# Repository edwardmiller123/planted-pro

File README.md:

# planted-pro
This is the planted-pro plant monitor. It is my first electronics project and the goal was to create a full product end to end (mostly) from scratch. The repo aims to provide all the resources needed to build your very own if you so wished.

There is also the [planted-pro companion app](https://github.com/edwardmiller123/planted-pro-app)! Special thanks to [my wife](https://github.com/LucyRMCodes) for helping with this.

## Firmware
### Requirements
- [ARM GNU Toolchain](https://developer.arm.com/downloads/-/gnu-rm) - download the correct one for your system
- make
	- If on windows you can use a windows version like [Gnuwin32](https://gnuwin32.sourceforge.net/packages/make.htm)

- A device with the STLINK firmware. (For flashing main board) This could be an [official STlink debugger](https://uk.rs-online.com/web/p/debuggers-in-circuit-emulators/1827791) or a [nucleo board](https://www.st.com/en/evaluation-tools/nucleo-f446re.html)
- [OpenOCD](https://openocd.org/pages/getting-openocd.html) (For flashing main board)
	- [STLINK Tools](https://github.com/stlink-org/stlink) - Optional alternative
- gdb-multiarch (for flashing and debugging)

### Building
Compile the firmware with,
```
make fw
```

By default the fw is compiled without any log lines and with the debug LED on the main board disabled. To enable these simply run,
```
make fw LOGLEVEL={log level} (-B)
```
where {log level} ranges from 0 to 4 with 0 being FATAL and 4 being DEBUG. You may need to force a full rebuild with `-B` for make to pick up the symbol changes.

### Flashing The Board

## Main board
### Requirements
- [Kicad](https://www.kicad.org/)
- make
	- If on windows you can use a windows version like [Gnuwin32](https://gnuwin32.sourceforge.net/packages/make.htm)

### Exporting Fabrication Files
The gerber and drill files for the main board can be exported from kicad by running,
```
make pcb
```
This will create a `zip` of all the nessecary files ready to be sent to your favourite PCB manufacturer.

### Schematic
You can export a `pdf` of the schematic with,
```
make schematic
```

## Case
The case was designed in Tinkercad. STL files can be found in the `case` directory but you can also play with the original project online [here](https://www.tinkercad.com/things/aGYA4L6WpCP-planted-pro-v3).
Included in the `case` directory is a project file for [Bambu Studio](https://bambulab.com/en/download/studio) as I was printing on a [Bambu X1 Carbon](https://uk.store.bambulab.com/collections/x1-series) at [work](https://www.codethink.co.uk/). If using a different printer youll need to do the slicing yourself or you can send the `stl` files off to your favourite printing house.

## Constructing

### Requirements
- See previous sections for software requirements

You can generate all the nessecary files for contruction all at once by running,
```
make all
```

A full parts list can be found [here](docs/parts_list.md) in the docs folder along with data sheets for the MCU/ICs on the board and any external modules. 

# TODO
- Decrease the resistor values on the battery charge monitor to reduce noise

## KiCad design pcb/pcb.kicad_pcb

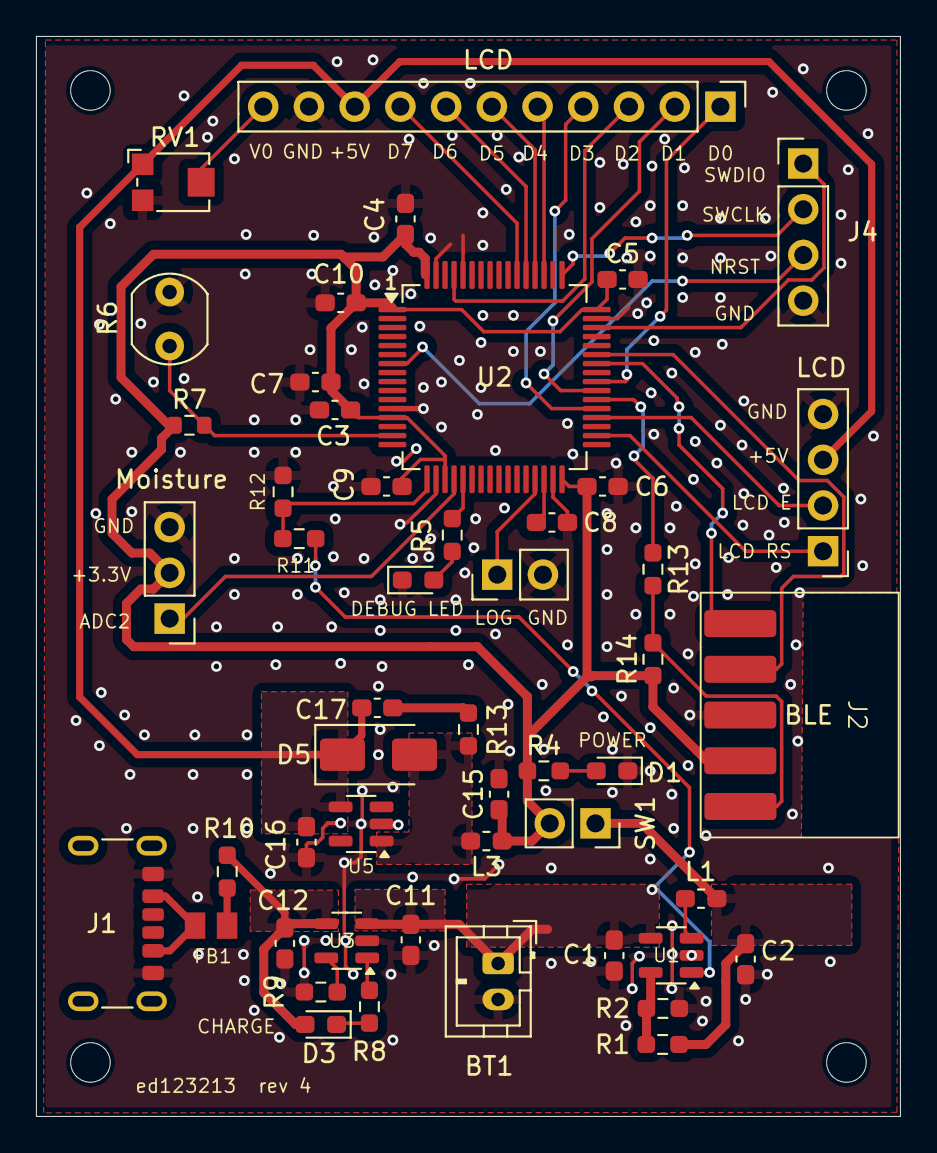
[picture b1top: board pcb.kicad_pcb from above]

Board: 2 copper layers, 48.0 x 60.0 mm, 51 parts (0 on the bottom side), 41 nets.

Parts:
2.2mm: MountingHole_2.2mm_M2_ISO7380
BT1: 4.2v Lipo; JST_PH_B2B-PH-K_1x02_P2.00mm_Vertical
C1, C3, C8, C11, C12: 4.7uF; C_0603_1608Metric_Pad1.08x0.95mm_HandSolder
C2, C15: 10uF; C_0603_1608Metric_Pad1.08x0.95mm_HandSolder
C4, C5, C6, C7, C9, C10: 100nF; C_0603_1608Metric_Pad1.08x0.95mm_HandSolder
C16: 22uF; C_0603_1608Metric_Pad1.08x0.95mm_HandSolder
C17: 1nF; C_0603_1608Metric_Pad1.08x0.95mm_HandSolder
D1: PWR LED; LED_0603_1608Metric_Pad1.05x0.95mm_HandSolder
D2: DEBUG LED; LED_0603_1608Metric_Pad1.05x0.95mm_HandSolder
D3: CHARGE LED; LED_0603_1608Metric_Pad1.05x0.95mm_HandSolder
D5: SS38; D_SMA
FB1: FerriteBead; BEADC2012X105N
J1: USB_C_Receptacle_USB2.0_14P; USB_C_Receptacle_GCT_USB4125-xx-x-0190_6P_TopMnt_Horizontal
J2: LCD; PinHeader_1x11_P2.54mm_Vertical
J2#2: VG6328A; Vollgo VG6328A
J4: LCD CTRL; PinHeader_1x04_P2.54mm_Vertical
J4#2: Debug; PinHeader_1x04_P2.54mm_Vertical
J5: Moisture; PinHeader_1x03_P2.54mm_Vertical
J6: Logs; PinHeader_1x02_P2.54mm_Vertical
L1, L3: 2.2uH; L_0603_1608Metric_Pad1.05x0.95mm_HandSolder
R1: 453k; R_0603_1608Metric_Pad0.98x0.95mm_HandSolder
R2, R14: 100k; R_0603_1608Metric_Pad0.98x0.95mm_HandSolder
R4, R5: 1.5k; R_0603_1608Metric_Pad0.98x0.95mm_HandSolder
R6: LDR07; R_LDR_5.0x4.1mm_P3mm_Vertical
R7: 200k; R_0603_1608Metric
R8, R13: 1k; R_0603_1608Metric_Pad0.98x0.95mm_HandSolder
R9: 2k; R_0603_1608Metric_Pad0.98x0.95mm_HandSolder
R10: 1; R_0603_1608Metric_Pad0.98x0.95mm_HandSolder
R11, R12: 50k; R_0603_1608Metric_Pad0.98x0.95mm_HandSolder
R13#2: 10; R_0603_1608Metric_Pad0.98x0.95mm_HandSolder
RV1: LCD Contrast; Potentiometer_Bourns_TC33X_Vertical
SW1: PWR SWITCH; PinSocket_1x02_P2.54mm_Vertical
U1: TLV62569DBV; SOT-23-5
U2: STM32F446RETx; LQFP-64_10x10mm_P0.5mm
U3: MCP73831-2-OT; SOT-23-5
U5: TPS613222ADBV; SOT-23-5

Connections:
+3.3V: C3.1, C4.1, C5.1, C6.1, C7.1, C9.1, C10.1, C15.1, J2#2.4, J5.2, L3.1, R4.2, R7.1, R14.1, SW1.2 (B), U2.1 (VBAT), U2.13 (VDDA), U2.19 (VDD), U2.32 (VDD), U2.48 (VDD), U2.64 (VDD)
+3.3Vswin: C2.1, L1.2, R1.1, SW1.1 (A)
+5V: C16.1, C17.2, D5.1 (K), J2.9, J4.3, RV1.1, U5.4 (VOUT)
+Vbat: BT1.1 (+), C1.1, C11.1, R11.1, U1.1 (EN), U1.4 (VIN), U3.3 (V_{BAT})
+Vext: C12.1, D3.2 (A), R10.2, U3.4 (V_{DD})
ADC1: R6.1, R7.2, U2.15 (PA1)
ADC2: J5.1, U2.20 (PA4)
ADC3: R11.2, R12.1, U2.17 (PA3)
BT CONNECT: R13.1, U2.38 (PC7)
DEBUG LED: R5.2, U2.21 (PA5)
GND: BT1.2 (-), C1.2, C2.2, C3.2, C4.2, C5.2, C6.2, C7.2, C8.2, C9.2, C10.2, C11.2, C12.2, C15.2, C16.2, D1.1 (K), D2.1 (K), J1.A12 (GND), J1.B12 (GND), J2.10, J2#2.3, J4.4, J4#2.4, J5.3, J6.2, R2.2, R6.2, R9.2, R12.2, RV1.3, U1.2 (GND), U2.12 (VSSA), U2.18 (VSS), U2.31 (VSS), U2.47 (VSS), U2.60 (BOOT0), U2.63 (VSS), U3.2 (V_{SS}), U5.2 (GND)
LCD D1: J2.1, U2.40 (PC9)
LCD D2: J2.2, U2.39 (PC8)
LCD D3: J2.3, U2.61 (PB8)
LCD D4: J2.4, U2.37 (PC6)
LCD D5: J2.5, U2.51 (PC10)
LCD D6: J2.6, U2.52 (PC11)
LCD D7: J2.7, U2.53 (PC12)
LCD D8: J2.8, U2.54 (PD2)
LCD E: J4.2, U2.36 (PB15)
LCD RS: J4.1, U2.34 (PB13)
NRST: J4#2.3, U2.7 (NRST)
unnamed: C17.1, R13#2.2
unnamed: D1.2 (A), R4.1
unnamed: D2.2 (A), R5.1
unnamed: D3.1 (K), R8.1
unnamed: D5.2 (A), L3.2, R13#2.1, U5.1 (SW)
unnamed: FB1.1, J1.A9 (VBUS), J1.B9 (VBUS)
unnamed: FB1.2, R10.1
unnamed: J2#2.5, R13.2, R14.2
unnamed: J2.11, RV1.2
unnamed: R1.2, R2.1, U1.5 (FB)
unnamed: L1.1, U1.3 (SW)
unnamed: C8.1, U2.30 (VCAP_1)
unnamed: R9.1, U3.5 (PROG)
unnamed: R8.2, U3.1 (STAT)
SWCLK: J4#2.2, U2.49 (PA14)
SWDIO: J4#2.1, U2.46 (PA13)
USART1 RX: J2#2.2, U2.43 (PA10)
USART1 TX: J2#2.1, U2.42 (PA9)
USART3 TX: J6.1, U2.29 (PB10)

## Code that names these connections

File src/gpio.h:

#ifndef LED_H
#define LED_H

#include <stdint.h>

#include "memmap.h"

typedef enum gpio {
	GPIOA,
	GPIOB,
	GPIOC,
	GPIOD
} gpio;

typedef enum gpio_action {
	CLEAR,
	SET
} gpio_action;

// alters the state the given pin in the given gpio port using the atomic BSSR register
void gpio_write_pin_atomic(gpio port, uint32_t pin, gpio_action action);

// GPIOA //

// base address of GPIOA port
#define GPIOA_BASE (AHB1_BASE + 0x0U)

#define GPIOA_MODER (GPIOA_BASE + 0x0U) // Output mode
#define GPIOA_OTYPER (GPIOA_BASE + 0x4U)
#define GPIOA_OSPEEDR (GPIOA_BASE + 0x8U)
#define GPIOA_PUPDR (GPIOA_BASE + 0x0CU)
#define GPIOA_AFRL (GPIOA_BASE + 0x20U) // Pin alternate functions 
#define GPIOA_AFRH (GPIOA_BASE + 0x24U) // Pin alternate functions 
#define GPIOA_ODR (GPIOA_BASE + 0x14U) // Output data register
#define GPIOA_BSSR (GPIOA_BASE + 0x18U) // Output data register

#define PA1 1
#define PA5 5

// GPIOB //

#define PB8 8
#define PB13 13
#define PB14 14
#define PB15 15

#define GPIOB_BASE (AHB1_BASE + 0x400U)

#define GPIOB_MODER (GPIOB_BASE + 0x0U)
#define GPIOB_OTYPER (GPIOB_BASE + 0x4U)
#define GPIOB_OSPEEDR (GPIOB_BASE + 0x8U)
#define GPIOB_PUPDR (GPIOB_BASE + 0x0CU)
#define GPIOB_AFRH (GPIOB_BASE + 0x24U)
#define GPIOB_ODR (GPIOB_BASE + 0x14U)
#define GPIOB_BSSR (GPIOB_BASE + 0x18U)

// GPIOC //

#define GPIOC_BASE (AHB1_BASE + 0x800U)

#define GPIOC_MODER (GPIOC_BASE + 0x0U)
#define GPIOC_OTYPER (GPIOC_BASE + 0x4U)
#define GPIOC_OSPEEDR (GPIOC_BASE + 0x8U)
#define GPIOC_PUPDR (GPIOC_BASE + 0x0CU)
#define GPIOC_AFRH (GPIOC_BASE + 0x24U)
#define GPIOC_ODR (GPIOC_BASE + 0x14U)
#define GPIOC_BSSR (GPIOC_BASE + 0x18U)

#define PC6 6
#define PC8 8
#define PC9 9
#define PC10 10
#define PC11 11
#define PC12 12

// GPIOD //

#define GPIOD_BASE (AHB1_BASE + 0xC00U)

#define GPIOD_MODER (GPIOD_BASE + 0x0U)
#define GPIOD_OTYPER (GPIOD_BASE + 0x4U)
#define GPIOD_OSPEEDR (GPIOD_BASE + 0x8U)
#define GPIOD_PUPDR (GPIOD_BASE + 0x0CU)
#define GPIOD_AFRH (GPIOD_BASE + 0x24U)
#define GPIOD_ODR (GPIOD_BASE + 0x14U)
#define GPIOD_BSSR (GPIOD_BASE + 0x18U)

#define PD2 2

// LED //

#define LED2 PA5

void toggle_user_led();

void init_user_led();

// Backup error signalling
void fast_blink();

#endif

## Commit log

2025-02-24 cleaner io port access
2025-03-14 add systick
2025-03-28 add sys_delay
2025-03-28 fix linker script variables
2025-03-31 initialise .data and .bss correctly
2025-04-04 init usart
2025-04-10 initialise usart1
2025-04-11 send buffer with usart
2025-04-12 add logger
2025-04-14 add software reset and fix some logging issues
2025-04-15 fix logger str concatenation
2025-04-19 start adding lcd driver
2025-04-26 fix lcd initialisation
2025-04-27 set cursor position
2025-04-27 improve str_cat
2025-04-28 fix .data section
2025-05-04 configure ADC
2025-05-04 add queue
2025-05-06 implement snsor polling logic
2025-05-09 fix light percentage calculation
2025-05-10 todos
2025-05-11 configure ADC2 and refactor
2025-05-11 add soil water monitor logic
2025-05-18 add lcd scrolling
2025-05-18 fix soil display
2025-05-18 update TODOs
2025-05-19 add todo
2025-05-20 fix ADC2
2025-05-21 fix git ignore
2025-05-21 add block diagram
2025-05-22 reorganise repo
2025-05-25 comments
2025-05-25 start pcb schematic
2025-05-26 refactor and fix water percentage
2025-05-26 add usart2 to schematic
2025-05-26 dont commit lock files
2025-05-27 fix converter in schematic
2025-05-29 update schematic and readme
2025-05-29 configure USART2 for TX
2025-05-31 configure usart3
2025-05-31 better use of pins
2025-05-31 refactor USART
2025-05-31 typo
2025-06-03 add list structure
2025-06-03 implement heap
2025-06-05 use heap for initilisations
2025-06-05 set queue capacity on initialisation
2025-06-06 fix heap alignment
2025-06-08 add export functionality
2025-06-08 add queue data persistence
2025-06-13 irqs
2025-06-13 implement ring buffer and export when commadn received
2025-06-14 fix json getting cut off
2025-06-15 fix hard fault
2025-06-15 fix bad water readings
2025-06-16 fix ts corruption
2025-06-16 fix ring buffer iteration
2025-06-16 fix spamming causing corruption
2025-06-16 fix zeros not showing
2025-06-16 read me update
2025-06-17 add battery charging circuit
2025-06-17 Add power and gnd pins for each component
2025-06-18 readme change
2025-06-18 small schematic tweaks
2025-06-18 fix charging circuit resistor
2025-06-19 start designing pcb
2025-06-20 arrange buck, charging circuit and f4
2025-06-21 add capacitors to cpu
2025-06-21 add pwr switch
2025-06-21 add traces for lcd rs re and hc-05
2025-06-22 finish pcb
2025-06-23 move capacitors closer
2025-06-24 switch to grouped headers
2025-06-25 fix pcb errors
2025-06-27 redesign charging circuit
2025-06-28 fix errors and add labels
2025-06-28 generate gerber files
2025-06-28 change name
2025-06-29 fix drc errors and add mount holes
2025-06-29 export gerber files
2025-06-29 update parts list
2025-06-30 add vcap capacitor and widen traces
2025-06-30 increase board outline
2025-07-01 change design to use 0402 for buck converter
2025-07-01 change buck divider resistors
2025-07-06 replace queues with ring buffers
2025-07-06 add debug makefile arg
2025-07-06 send current reading along with historical data
2025-07-07 fix ringbuffer iteration
2025-07-09 add dimensions to readme
2025-07-09 update case dimensions
2025-07-12 add more dimensions
2025-07-16 add case note
2025-07-16 update case measurements
2025-07-19 add case stl files
2025-07-27 add lid window for charge led
2025-08-04 fix buck converter trace and add gerbers
2025-08-10 add taller case
2025-08-11 Add notes
2025-08-12 add review notes to implement
2025-08-13 start adding boost converter
2025-08-15 add boost converter to schematic
2025-08-15 redo case screw holes
2025-08-16 add boost converter voltage divider
2025-08-18 add review notes
2025-08-19 review notes: use alternative boost converter chip
2025-08-19 re-do boost converter
2025-08-19 add footprints and update parts list
2025-08-19 start re-designing pcb
2025-08-20 more pcb redesign
2025-08-23 add resonance to schematic
2025-08-23 finish revision 2
2025-08-26 add bambu project file for case
2025-08-26 add case review notes
2025-08-27 case v1.4
2025-08-27 Add rev number to board
2025-08-28 review notes and re slice case
2025-08-29 add power plane on boost converter input
2025-08-29 adjust case lid
2025-08-29 Add case V2
2025-08-29 mark pin 1 on stm32f4
2025-08-31 add git sha to export payload
2025-09-01 review notes
2025-09-01 redo bambu project file
2025-09-02 update bambu project and add review notes
2025-09-02 start adding real uni time
2025-09-02 add charge sensor to schematic
2025-09-03 Add battery sensor to pcb
2025-09-03 fix git sha not showing
2025-09-04 more review notes
2025-09-05 Make power traces better on pcb
2025-09-05 Add case v2.1
2025-09-05 fix invlaid json
2025-09-07 case v2.2
2025-09-07 Read and sync clock with external time
2025-09-07 move linker script
2025-09-08 Add pcb export to makefile
2025-09-09 update readme and makefile
2025-09-09 Add more vias
2025-09-09 Add more vias and input capacitor to schematic
2025-09-10 add input capacitor to boost converter
2025-09-10 better output labels in makefile
2025-09-10 Add volgo bluetooth module to pcb
2025-09-12 Improve volgo bluetooth footprint and add pull up for bt connect pin
2025-09-12 case v3
2025-09-12 separate bluetooth and export logic
2025-09-12 re generate gerbers
2025-09-12 design plans
2025-09-15 move vias closer together
2025-09-15 remove gnd plane under antenna correctly
2025-09-20 Add battery monitor logic
2025-09-21 make better space for antenna
2025-09-21 add gnd sockets to debug headers
2025-09-21 tidy schematic
2025-09-22 Add build directory to make file
2025-09-24 fix charge message not displaying
2025-09-27 Add bluetooth connection message logic
2025-09-28 more efficient logging
2025-09-30 case design change notes
2025-09-30 case 3.x changes
2025-10-01 add case v 3.3 and more review notes
2025-10-03 Case changes: body-v3.4, usb-cap-v3.2, lid-v3.3
2025-10-14 fix incorrect labels on schematic
2025-10-17 Add lid v3.4
2025-10-17 change bluetooth baud
2025-10-21 dont use internal pull up onPA5 for debug LED
2025-10-21 Add lid v3.4 to 3d print project file
2025-10-22 Enable clock for SYSCFG on ABP2 bus
2025-10-24 Set BLE name on startup
2025-10-24 silence unused variable warnings for log line args
2025-10-24 base water level off percent rather than raw value
2025-10-24 set light levels based off percentages and fix water levels
2025-10-25 add usb cap v3.3
2025-11-04 Add todo notes
2025-11-06 Add usb-cap to bambu project file
2025-11-07 disable spp broadcast on startup
2025-11-07 fix bluetooth connected message
2025-11-07 fix int overflow in ring buffer
2025-11-07 Add case lid and body v3.5
2025-11-07 Add hardware reference docs
2025-11-07 Start writing readme
2025-11-07 remove old diagrams
2025-11-09 add gdb script
2025-11-09 Add schematic pdf to makefile
2025-11-09 change schematic name
2025-11-09 Typos in readme
2025-11-09 rename src dir
2025-11-14 Use internal refernce voltage to calculate battey charge
2025-11-14 change resistor values on bat monitor
2025-11-14 take average bat percent from 3 readings
